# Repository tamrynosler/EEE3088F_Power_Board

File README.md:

# Micro-Mouse Design Project - KiCad Files

## 📖 Overview
This repository contains documentation, schematics, and PCB files used during the design of the Micro-Mouse Power Board.
There were a few issues with our original KiCad file getting corrupted so we had to copy its contents into a new KiCad project file.

## 📁 Important Files

The most recent and completed version of the project files can be found along the following file path:
- `Power Board/EEE3088F Power Board/NEW_KICAD` – Main KiCad project files (schematic, PCB, BOM etc...)

This 'NEW_KICAD' folder contains:
- Project files (schematic and PCB)
- Imported footprint and symbol files
- Production Files in `Power Board/EEE3088F Power Board/NEW_KICAD/jlcpcb/production_files` (BOM, CPL, GERBER files)
- A few other 3D Model and library files we made trying to import random things (Please forgive us if this is a mess, most of the importing was done at 3am ;) )

## 👥 Authors

- Tamryn Osler; OSLTAM001 (@tamrynosler)
- Glen Jones; JNSGLE007 (@githubusername)

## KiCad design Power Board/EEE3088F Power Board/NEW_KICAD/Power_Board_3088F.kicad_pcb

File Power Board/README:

This Repo contains the KiCad files associated with a UCT EEE3088F micro-mouse power subsystem design.

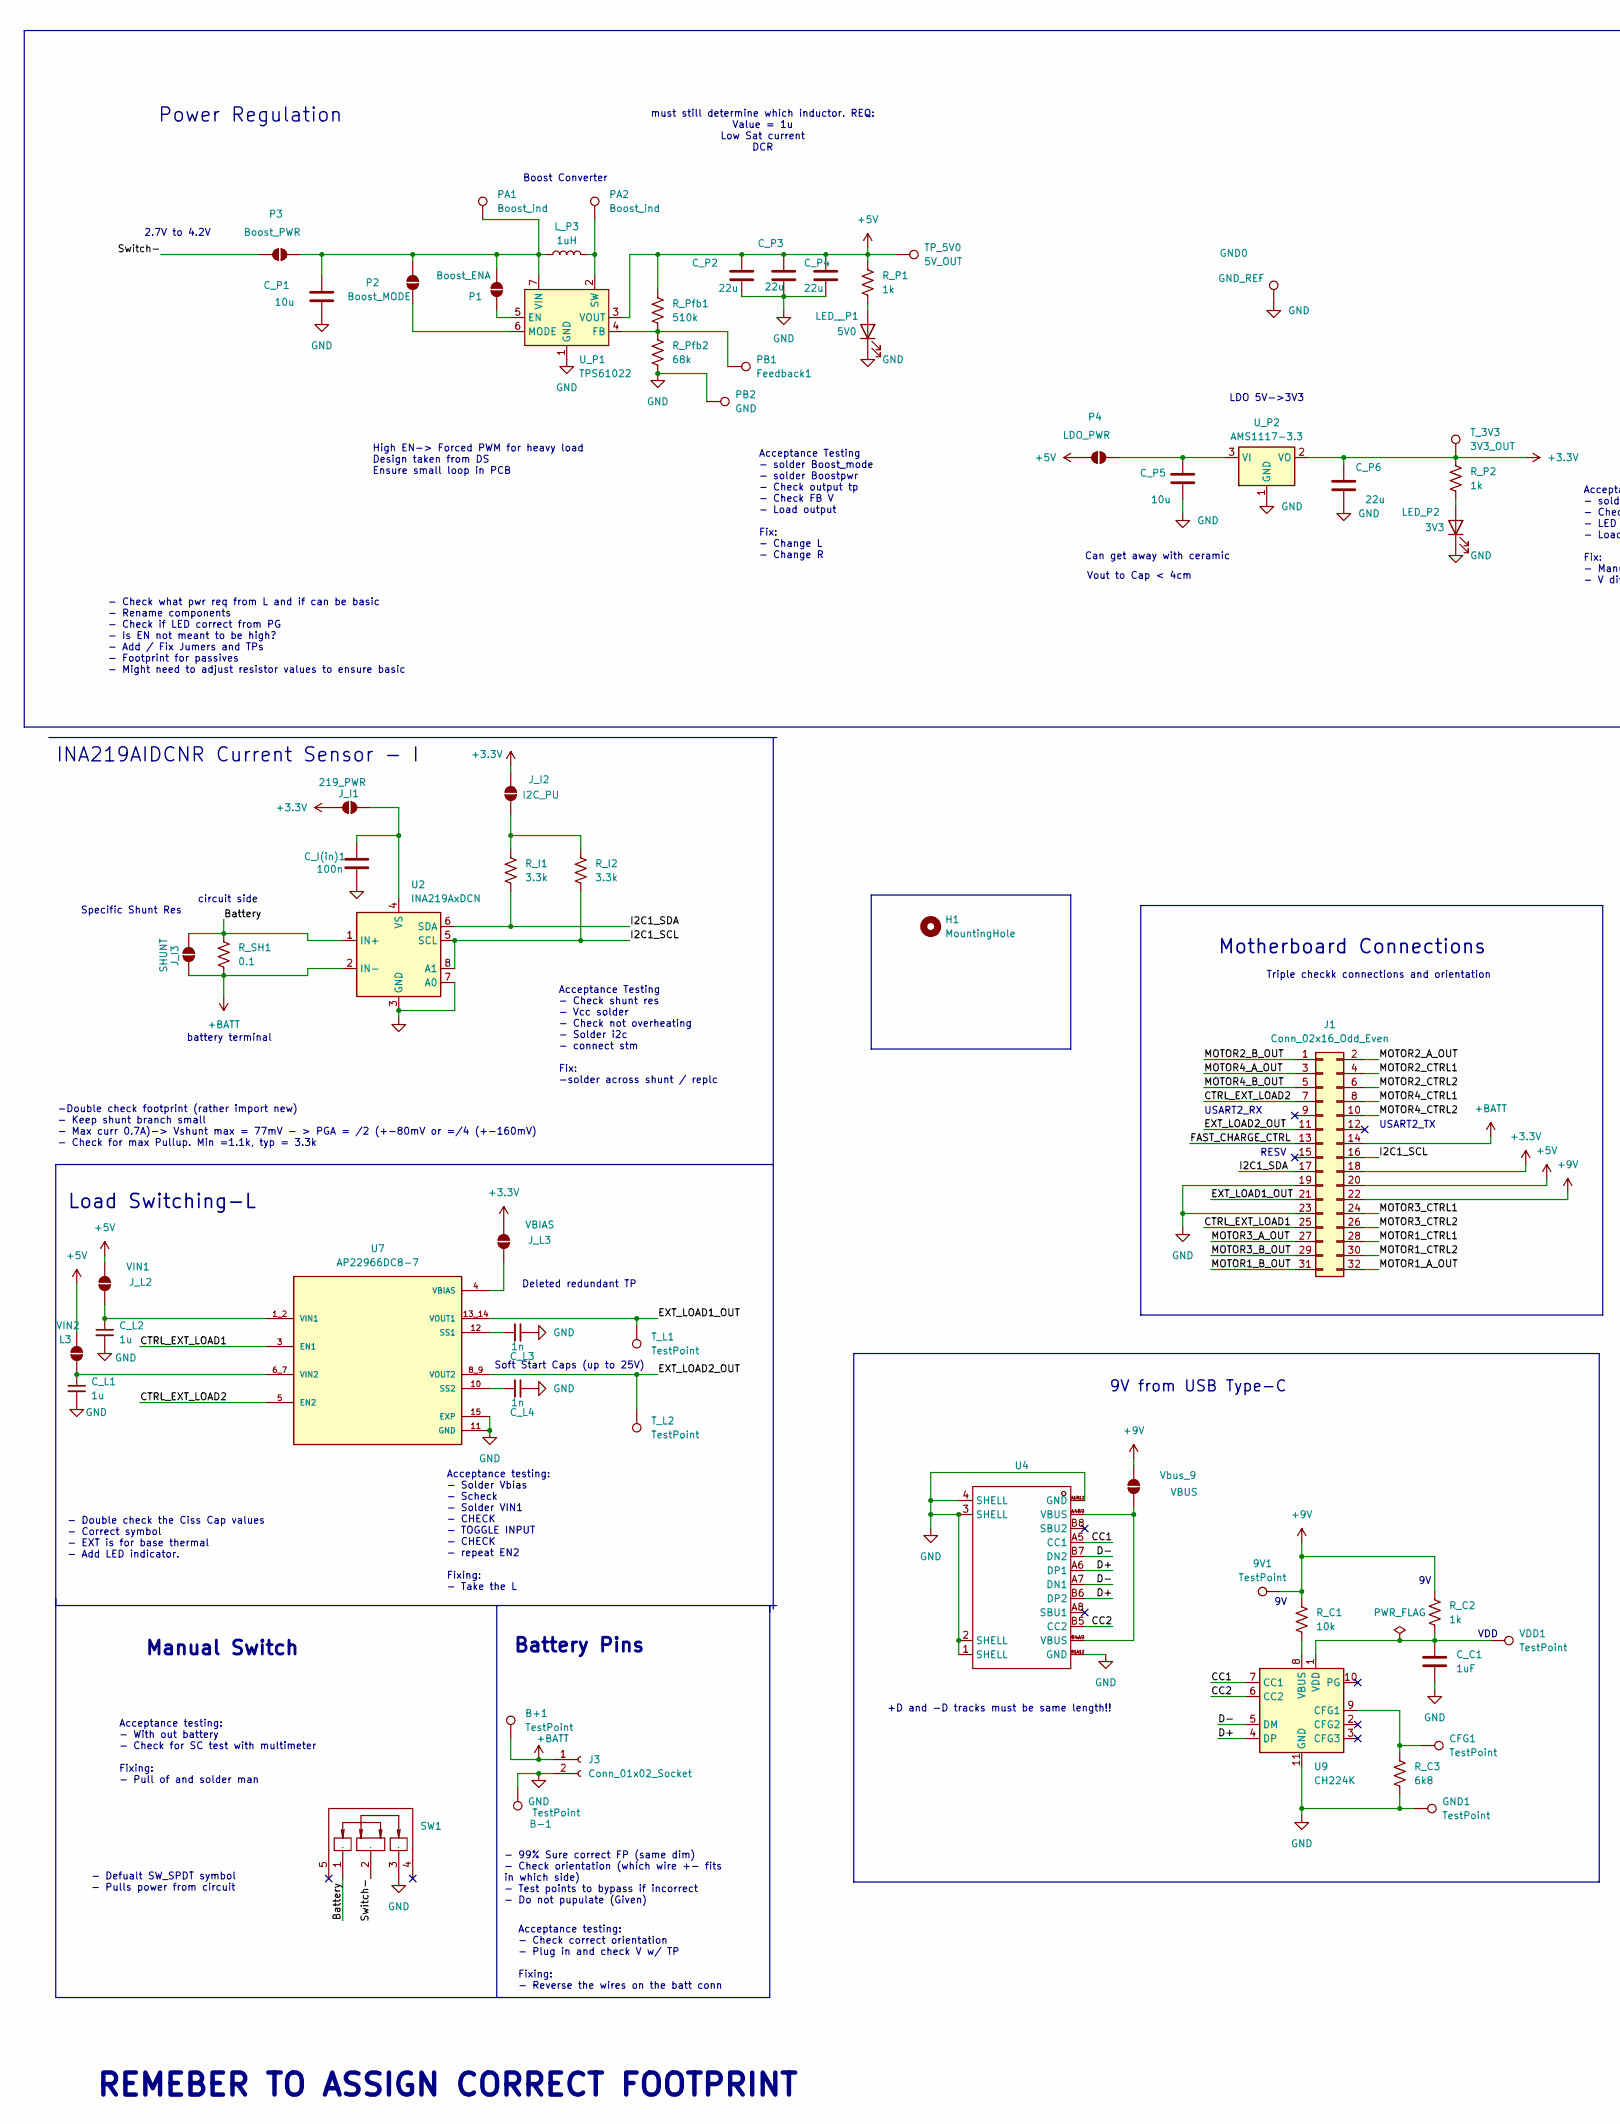
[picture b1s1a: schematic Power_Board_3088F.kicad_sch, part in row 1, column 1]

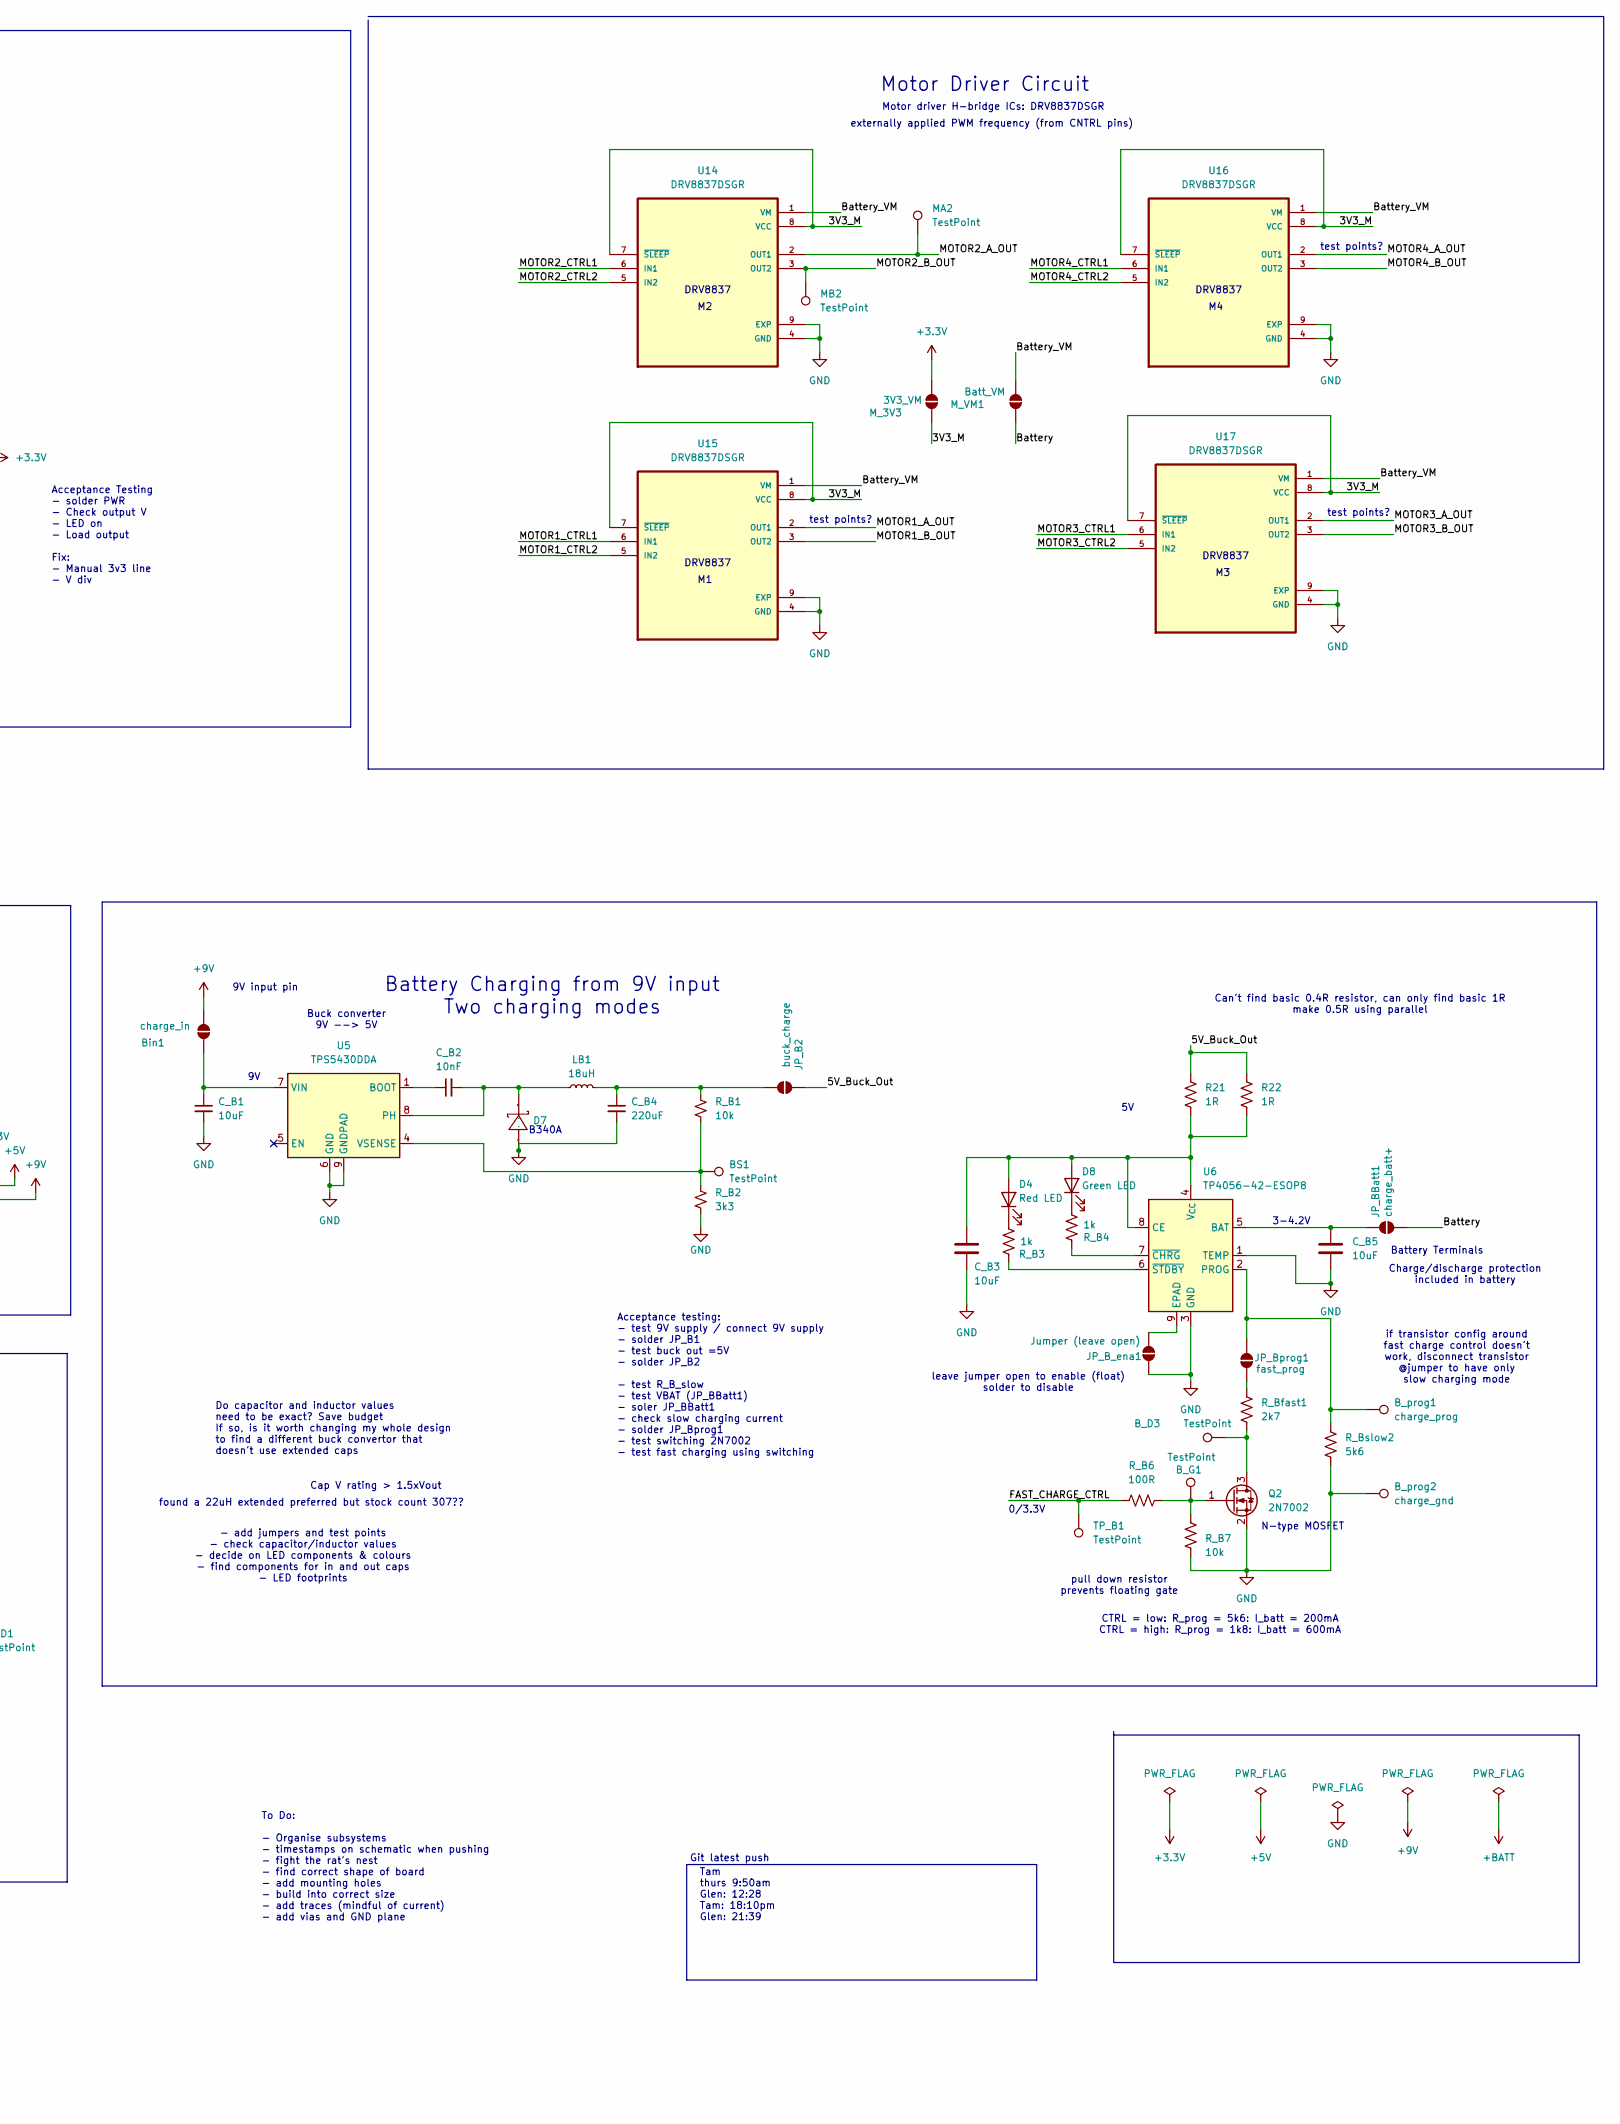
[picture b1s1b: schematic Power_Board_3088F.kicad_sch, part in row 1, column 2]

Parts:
3V3: LED_P2; LED_0603_1608Metric_Pad1.05x0.95mm_HandSolder
5V0: LED__P1; LED_0603_1608Metric_Pad1.05x0.95mm_HandSolder
9V1: TestPoint; TestPoint_Pad_D2.0mm
B+1: TestPoint; TestPoint_Pad_D2.0mm
B-1: TestPoint; TestPoint_Pad_D2.0mm
BS1: TestPoint; TestPoint_Pad_D2.0mm
B_D3: TestPoint; TestPoint_Pad_D2.0mm
B_G1: TestPoint; TestPoint_Pad_D2.0mm
B_prog1: charge_prog; TestPoint_Pad_D2.0mm
B_prog2: charge_gnd; TestPoint_Pad_D2.0mm
Bin1: charge_in; SolderJumper-2_P1.3mm_Open_RoundedPad1.0x1.5mm
CFG1: TestPoint; TestPoint_Pad_D2.0mm
C_B1: 10uF; C_1206_3216Metric_Pad1.33x1.80mm_HandSolder
C_B2: 10nF; C_0603_1608Metric_Pad1.08x0.95mm_HandSolder
C_B3, C_B5: 10uF; C_0603_1608Metric_Pad1.08x0.95mm_HandSolder
C_B4: 220uF; CP_Elec_6.3x7.7
C_C1: 1uF; C_0603_1608Metric_Pad1.08x0.95mm_HandSolder
C_I(in)1: 100n; C_0603_1608Metric_Pad1.08x0.95mm_HandSolder
C_L1, C_L2: 1u; C_0603_1608Metric_Pad1.08x0.95mm_HandSolder
C_L3, C_L4: 1n; C_0603_1608Metric_Pad1.08x0.95mm_HandSolder
C_P1, C_P5: 10u; C_0603_1608Metric_Pad1.08x0.95mm_HandSolder
C_P2, C_P3, C_P4, C_P6: 22u; C_0603_1608Metric_Pad1.08x0.95mm_HandSolder
D4: Red LED; LED_0603_1608Metric_Pad1.05x0.95mm_HandSolder; JLCPCB Part # C2286
D7: BA340A; B340A; Manufacturer Part B340A; LCSC Part Name 电压:40V 电流:3A
D8: Green LED; LED_0603_1608Metric_Pad1.05x0.95mm_HandSolder; JLCPCB Part # C2297
GND0: GND_REF; TestPoint_Pad_D2.0mm
GND1: TestPoint; TestPoint_Pad_D2.0mm
H1: MountingHole; MountingHole_3.2mm_M3
J1: Conn_02x16_Odd_Even; PinHeader_2x16_P2.54mm_Vertical
J3: Conn_01x02_Socket; JST_PH_S2B-PH-K_1x02_P2.00mm_Horizontal
JP_B2: buck_charge; SolderJumper-2_P1.3mm_Open_RoundedPad1.0x1.5mm
JP_BBatt1: charge_batt+; SolderJumper-2_P1.3mm_Open_RoundedPad1.0x1.5mm
JP_B_ena1: Jumper (leave open); SolderJumper-2_P1.3mm_Open_RoundedPad1.0x1.5mm
JP_Bprog1: fast_prog; SolderJumper-2_P1.3mm_Open_RoundedPad1.0x1.5mm
J_I1: 219_PWR; SolderJumper-2_P1.3mm_Open_RoundedPad1.0x1.5mm
J_I2: I2C_PU; SolderJumper-2_P1.3mm_Open_RoundedPad1.0x1.5mm
J_I3: SHUNT; SolderJumper-2_P1.3mm_Open_RoundedPad1.0x1.5mm
J_L2: VIN1; SolderJumper-2_P1.3mm_Open_RoundedPad1.0x1.5mm
J_L3: VBIAS; SolderJumper-2_P1.3mm_Open_RoundedPad1.0x1.5mm
L3: VIN2; SolderJumper-2_P1.3mm_Open_RoundedPad1.0x1.5mm
LB1: 18uH; L_Abracon_ASPI-4030S
L_P3: 1uH; L_Changjiang_FXL0630
MA2: TestPoint; TestPoint_Pad_D2.0mm
MB2: TestPoint; TestPoint_Pad_D2.0mm
M_3V3: 3V3_VM; SolderJumper-2_P1.3mm_Open_RoundedPad1.0x1.5mm
M_VM1: Batt_VM; SolderJumper-2_P1.3mm_Open_RoundedPad1.0x1.5mm
P1: Boost_ENA; SolderJumper-2_P1.3mm_Open_RoundedPad1.0x1.5mm
P2: Boost_MODE; SolderJumper-2_P1.3mm_Open_RoundedPad1.0x1.5mm
P3: Boost_PWR; SolderJumper-2_P1.3mm_Open_RoundedPad1.0x1.5mm
P4: LDO_PWR; SolderJumper-2_P1.3mm_Open_RoundedPad1.0x1.5mm
PA1, PA2: Boost_ind; TestPoint_Pad_D2.0mm
PB1: Feedback1; TestPoint_Pad_D2.0mm
PB2: GND; TestPoint_Pad_D2.0mm
Q2: 2N7002; SOT-23
R21, R22: 1R; R_0603_1608Metric_Pad0.98x0.95mm_HandSolder
R_B1, R_B7: 10k; R_0603_1608Metric_Pad0.98x0.95mm_HandSolder
R_B2: 3k3; R_0603_1608Metric_Pad0.98x0.95mm_HandSolder
R_B3, R_B4: 1k; R_0603_1608Metric_Pad0.98x0.95mm_HandSolder
R_B6: 100R; R_0603_1608Metric_Pad0.98x0.95mm_HandSolder
R_Bfast1: 2k7; R_0603_1608Metric_Pad0.98x0.95mm_HandSolder
R_Bslow2: 5k6; R_0603_1608Metric_Pad0.98x0.95mm_HandSolder
R_C1: 10k; R_0603_1608Metric_Pad0.98x0.95mm_HandSolder
R_C2: 1k; R_0603_1608Metric_Pad0.98x0.95mm_HandSolder
R_C3: 6k8; R_0603_1608Metric_Pad0.98x0.95mm_HandSolder
R_I1, R_I2: 3.3k; R_0603_1608Metric_Pad0.98x0.95mm_HandSolder
R_P1, R_P2: 1k; R_0603_1608Metric_Pad0.98x0.95mm_HandSolder
R_Pfb1: 510k; R_0603_1608Metric_Pad0.98x0.95mm_HandSolder
R_Pfb2: 68k; R_0603_1608Metric_Pad0.98x0.95mm_HandSolder
R_SH1: 0.1; R_1206_3216Metric_Pad1.30x1.75mm_HandSolder
SW1: SW-TH_SS-12D11G5; Manufacturer Part SS-12D11G5; LCSC Part Name 柄长5mm 弯插双档 滑动开关
TP_5V0: 5V_OUT; TestPoint_Pad_D2.0mm
TP_B1: TestPoint; TestPoint_Pad_D2.0mm
T_3V3: 3V3_OUT; TestPoint_Pad_D2.0mm
T_L1, T_L2: TestPoint; TestPoint_Pad_D2.0mm
U2: INA219AxDCN; SOT-23-8
U4: USB-C-SMD_G-SWITCH_GT-USB-7010ASV; Manufacturer Part GT-USB-7010ASV; LCSC Part Name Type-C 母 卧贴
U5: TPS5430DDA; SOIC-8-1EP_3.9x4.9mm_P1.27mm_EP2.29x3mm
U6: TP4056-42-ESOP8; SOIC127P600X175-9N
U7: AP22966DC8-7; IC_AP22966DC8-7; PARTREV 3-2
U9: CH224K; SSOP-10-1EP_3.9x4.9mm_P1mm_EP2.1x3.3mm
U14, U15, U16, U17: DRV8837DSGR; SON50P200X200X80-9N; DigiKey_Part_Number 296-34806-2-ND
U_P1: TPS61022; Texas_RWU0007A_VQFN-7_2x2mm_P0.5mm
U_P2: AMS1117-3.3; SOT-223-3_TabPin2
VDD1: TestPoint; TestPoint_Pad_D2.0mm
Vbus_9: VBUS; SolderJumper-2_P1.3mm_Open_RoundedPad1.0x1.5mm

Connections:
+3.3V: C_P6.2, J1.18, J_I1.1 (A), J_I2.1 (A), J_L3.2 (B), M_3V3.2 (B), R_P2.1, T_3V3.1, U_P2.2 (VO)
+5V: C_P2.2, C_P3.2, C_P4.2, J1.20, J_L2.2 (B), L3.2 (B), P4.2 (B), R_P1.1, R_Pfb1.1, TP_5V0.1, U_P1.3 (VOUT)
+9V: 9V1.1, Bin1.2 (B), J1.22, R_C1.1, R_C2.1, Vbus_9.1 (A)
+BATT: B+1.1, J1.14, J3.1, J_I3.1 (A), R_SH1.2, U2.2 (IN-)
/3V3_M: M_3V3.1 (A), U14.7 (~SLEEP), U14.8 (VCC), U15.7 (~SLEEP), U15.8 (VCC), U16.7 (~SLEEP), U16.8 (VCC), U17.7 (~SLEEP), U17.8 (VCC)
/5V_Buck_Out: JP_B2.1 (A), R21.1, R22.1
/Battery: JP_BBatt1.2 (B), J_I3.2 (B), M_VM1.1 (A), R_SH1.1, SW1.1, U2.1 (IN+)
/Battery_VM: M_VM1.2 (B), U14.1 (VM), U15.1 (VM), U16.1 (VM), U17.1 (VM)
/CC1: U4.A5 (CC1), U9.7 (CC1)
/CC2: U4.B5 (CC2), U9.6 (CC2)
/CTRL_EXT_LOAD1: J1.25, U7.3 (EN1)
/CTRL_EXT_LOAD2: J1.7, U7.5 (EN2)
/D+: U4.A6 (DP1), U4.B6 (DP2), U9.4 (DP)
/D-: U4.A7 (DN1), U4.B7 (DN2), U9.5 (DM)
/EXT_LOAD1_OUT: J1.21, T_L1.1, U7.13_14 (VOUT1)
/EXT_LOAD2_OUT: J1.11, T_L2.1, U7.8_9 (VOUT2)
/FAST_CHARGE_CTRL: J1.13, R_B6.1, TP_B1.1
/I2C1_SCL: J1.16, R_I2.2, U2.5 (SCL), U2.8 (A1)
/I2C1_SDA: J1.17, R_I1.2, U2.6 (SDA)
/MOTOR1_A_OUT: J1.32, U15.2 (OUT1)
/MOTOR1_B_OUT: J1.31, U15.3 (OUT2)
/MOTOR1_CTRL1: J1.28, U15.6 (IN1)
/MOTOR1_CTRL2: J1.30, U15.5 (IN2)
/MOTOR2_A_OUT: J1.2, MA2.1, U14.2 (OUT1)
/MOTOR2_B_OUT: J1.1, MB2.1, U14.3 (OUT2)
/MOTOR2_CTRL1: J1.4, U14.6 (IN1)
/MOTOR2_CTRL2: J1.6, U14.5 (IN2)
/MOTOR3_A_OUT: J1.27, U17.2 (OUT1)
/MOTOR3_B_OUT: J1.29, U17.3 (OUT2)
/MOTOR3_CTRL1: J1.24, U17.6 (IN1)
/MOTOR3_CTRL2: J1.26, U17.5 (IN2)
/MOTOR4_A_OUT: J1.3, U16.2 (OUT1)
/MOTOR4_B_OUT: J1.5, U16.3 (OUT2)
/MOTOR4_CTRL1: J1.8, U16.6 (IN1)
/MOTOR4_CTRL2: J1.10, U16.5 (IN2)
/Switch-: P3.2 (B), SW1.2
<NO NET>: C_I(in)1.1, U2.3 (GND), U2.7 (A0)
GND: 3V3.1 (K), 5V0.1 (K), B-1.1, B_prog2.1, C_B1.2, C_B3.2, C_B4.2, C_B5.2, C_C1.2, C_L1.2, C_L2.2, C_L3.1, C_L4.1, C_P1.1, C_P2.1, C_P3.1, C_P4.1, C_P5.1, C_P6.1, D7.2 (A), GND0.1, GND1.1, J1.19, J1.23, J3.2, JP_B_ena1.1 (A), PB2.1, Q2.2 (S), R_B2.2, R_B7.2, R_Bslow2.2, R_C3.2, R_Pfb2.2, SW1.3, U4.1 (SHELL), U4.2 (SHELL), U4.3 (SHELL), U4.4 (SHELL), U4.A1B12 (GND), U4.B1A12 (GND), U5.6 (GND), U5.9 (GNDPAD), U6.1 (TEMP), U6.3 (GND), U7.11 (GND), U7.15 (EXP), U9.11 (GND), U14.4 (GND), U14.9 (EXP), U15.4 (GND), U15.9 (EXP), U16.4 (GND), U16.9 (EXP), U17.4 (GND), U17.9 (EXP), U_P1.1 (GND), U_P2.1 (GND)
unnamed: 3V3.2 (A), R_P2.2
unnamed: 5V0.2 (A), R_P1.2
unnamed: Bin1.1 (A), C_B1.1, U5.7 (VIN)
unnamed: C_B3.1, D4.2 (A), D8.2 (A), R21.2, R22.2, U6.4 (V_{CC}), U6.8 (CE)
unnamed: D4.1 (K), R_B3.1
unnamed: C_B2.2, D7.1 (K), LB1.1, U5.8 (PH)
unnamed: D8.1 (K), R_B4.1
unnamed: C_B4.1, JP_B2.2 (B), LB1.2, R_B1.1
unnamed: C_B5.1, JP_BBatt1.1 (A), U6.5 (BAT)
unnamed: JP_B_ena1.2 (B), U6.9 (EPAD)
unnamed: B_prog1.1, JP_Bprog1.1 (A), R_Bslow2.1, U6.2 (PROG)
unnamed: JP_Bprog1.2 (B), R_Bfast1.1
unnamed: C_I(in)1.2, J_I1.2 (B), U2.4 (VS)
unnamed: J_I2.2 (B), R_I1.1, R_I2.1
unnamed: C_L2.1, J_L2.1 (A), U7.1_2 (VIN1)
unnamed: J_L3.1 (A), U7.4 (VBIAS)
unnamed: C_L1.1, L3.1 (A), U7.6_7 (VIN2)
unnamed: C_P1.2, L_P3.1, P1.1 (A), P2.2 (B), P3.1 (A), PA1.1, U_P1.7 (VIN)
unnamed: P1.2 (B), U_P1.5 (EN)
unnamed: P2.1 (A), U_P1.6 (MODE)
unnamed: C_P5.2, P4.1 (A), U_P2.3 (VI)
unnamed: B_D3.1, Q2.3 (D), R_Bfast1.2
unnamed: B_G1.1, Q2.1 (G), R_B6.2, R_B7.1
unnamed: C_B2.1, U5.1 (BOOT)
unnamed: BS1.1, R_B1.2, R_B2.1, U5.4 (VSENSE)
unnamed: R_B4.2, U6.7 (~CHRG)
unnamed: R_B3.2, U6.6 (~STDBY)
unnamed: C_L3.2, U7.12 (SS1)
unnamed: C_L4.2, U7.10 (SS2)
unnamed: CFG1.1, R_C3.1, U9.9 (CFG1)
unnamed: R_C1.2, U9.8 (VBUS)
unnamed: C_C1.1, R_C2.2, U9.1 (VDD), VDD1.1
unnamed: PB1.1, R_Pfb1.2, R_Pfb2.1, U_P1.4 (FB)
unnamed: L_P3.2, PA2.1, U_P1.2 (SW)
unnamed: U4.A4B9 (VBUS), U4.B4A9 (VBUS), Vbus_9.2 (B)

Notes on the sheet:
found a 22uH extended preferred but stock count 307??
3-4.2V
REMEBER TO ASSIGN CORRECT FOOTPRINT
test points?
if transistor config around fast charge control doesn't work, disconnect transistor @jumper to have only slow charging mode
Acceptance testing: - test 9V supply / connect 9V supply - solder JP_B1 - test buck out =5V - solder JP_B2 - test R_B_slow - test VBAT (JP_BBatt1) - soler JP_BBatt1 - check slow charging current - solder JP_Bprog1 - test switching 2N7002 - test fast charging using switching
0/3.3V
DRV8837
Battery Charging from 9V input Two charging modes
High EN-> Forced PWM for heavy load Design taken from DS Ensure small loop in PCB
USART2_RX
Manual Switch
Load Switching-L
-Double check footprint (rather import new) - Keep shunt branch small - Max curr 0.7A)-> Vshunt max = 77mV - > PGA = /2 (+-80mV or =/4 (+-160mV) - Check for max Pullup. Min =1.1k, typ = 3.3k
INA219AIDCNR Current Sensor - I
battery terminal
Acceptance testing: - Check correct orientation - Plug in and check V w/ TP Fixing: - Reverse the wires on the batt conn
Vout to Cap < 4cm
Motherboard Connections
N-type MOSFET
+D and -D tracks must be same length!!
Battery Terminals
Power Regulation
Deleted redundant TP
must still determine which inductor. REQ: Value = 1u Low Sat current DCR
Battery Pins
circuit side
2.7V to 4.2V
USART2_TX
- add jumpers and test points - check capacitor/inductor values - decide on LED components & colours - find components for in and out caps - LED footprints
9V from USB Type-C
9V input pin
LDO 5V->3V3
Can't find basic 0.4R resistor, can only find basic 1R make 0.5R using parallel
pull down resistor prevents floating gate
- Defualt SW_SPDT symbol - Pulls power from circuit
Acceptance Testing - solder PWR - Check output V - LED on - Load output Fix: - Manual 3v3 line - V div
B340A
RESV
Acceptance Testing - solder Boost_mode - solder Boostpwr - Check output tp - Check FB V - Load output Fix: - Change L - Change R

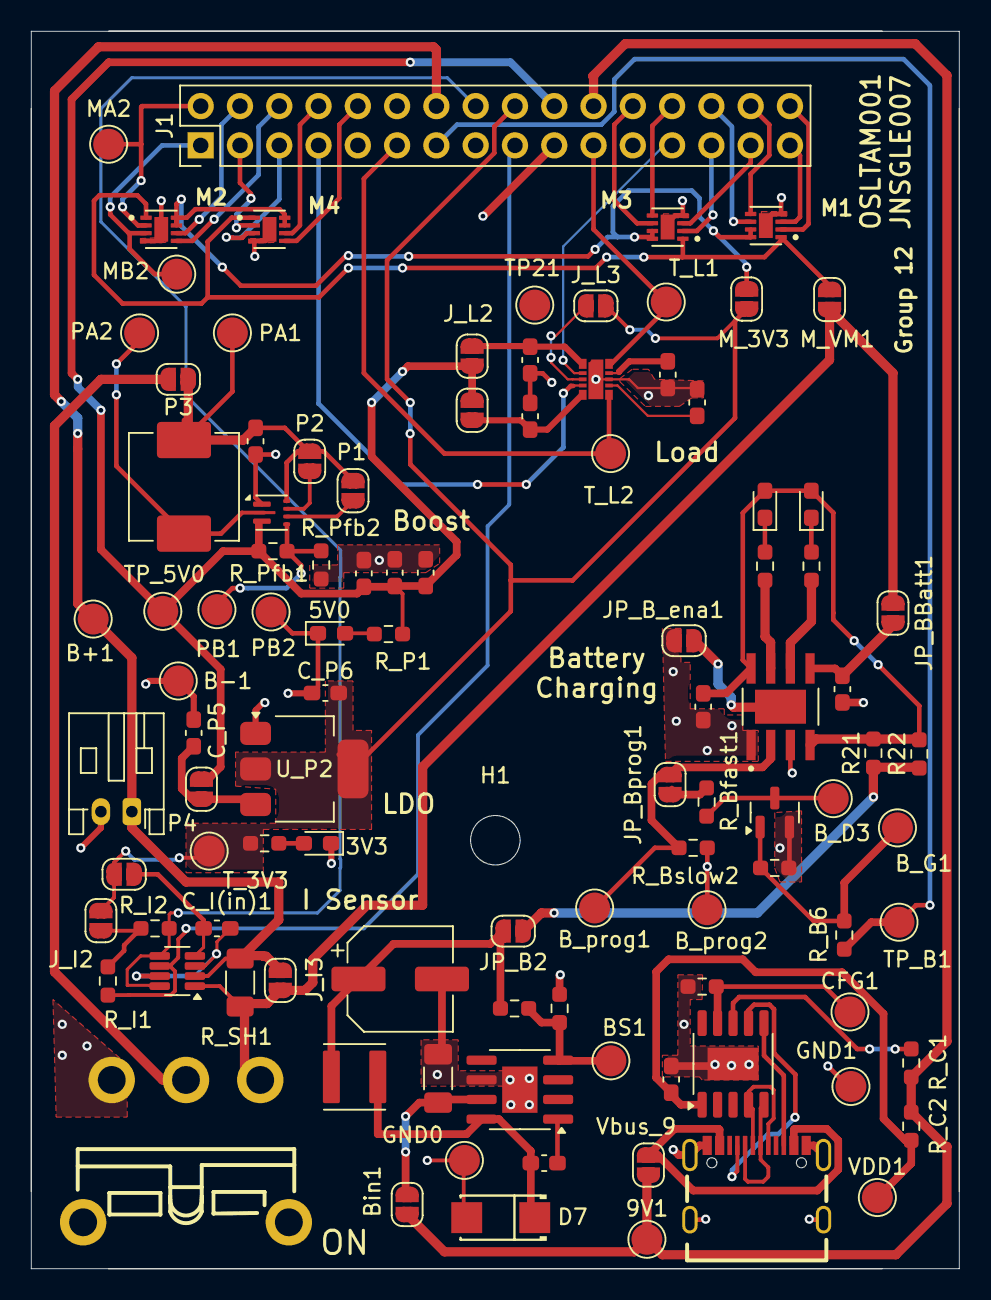
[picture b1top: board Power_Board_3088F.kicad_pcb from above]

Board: 2 copper layers, 60.0 x 80.0 mm, 103 parts (0 on the bottom side), 73 nets.

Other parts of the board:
TP21: TestPoint; TestPoint_Pad_D2.0mm

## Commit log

2025-03-22 Finished INA219 and schem layout
2025-03-22 added battery charging and started motor drivers
2025-03-23 Deleted EEE3088F Breadboard Design directory (unnecessary files)
2025-03-23 Deleted Power Board Personal directory (unnecessary files)
2025-03-23 finished motor driver circuit
2025-03-23 3v3 and some footprints complete
2025-03-23 Finished USB Type-C, added test points
2025-03-24 Basic schematic finished
2025-03-24 annotations, test points
2025-03-24 checked FP PWR reg and Curr Sens
2025-03-24 IC and passive component footprints added
2025-03-25 more labels and footprints
2025-03-25 notes and checked. SW FP to o
2025-03-25 added footprints and fixed buck
2025-03-25 Added com file
2025-03-26 Fixed communal fp and symbols
2025-03-26 ELC checks
2025-03-26 fixed footprints and symbols
2025-03-26 still no footprints on pcb editor (mac error)
2025-03-26 killing the mac version
2025-03-26 New windows Kicad ;)
2025-03-26 Added USB-C
2025-03-26 finished schematic
2025-03-26 pcb islands done
2025-03-27 arranged rats nest Tam
2025-03-27 Glen finished organising PCB & some 3D
2025-03-27 traces started
2025-03-27 Mostly finished Schem
2025-03-28 final v0
